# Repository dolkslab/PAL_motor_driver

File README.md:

# PAL_motor_driver

Brushed DC motor driver for RSA PAL robot. Based on arduino nano/uno + 2 DRV8871 modules to drive 24v/50W DC motors.

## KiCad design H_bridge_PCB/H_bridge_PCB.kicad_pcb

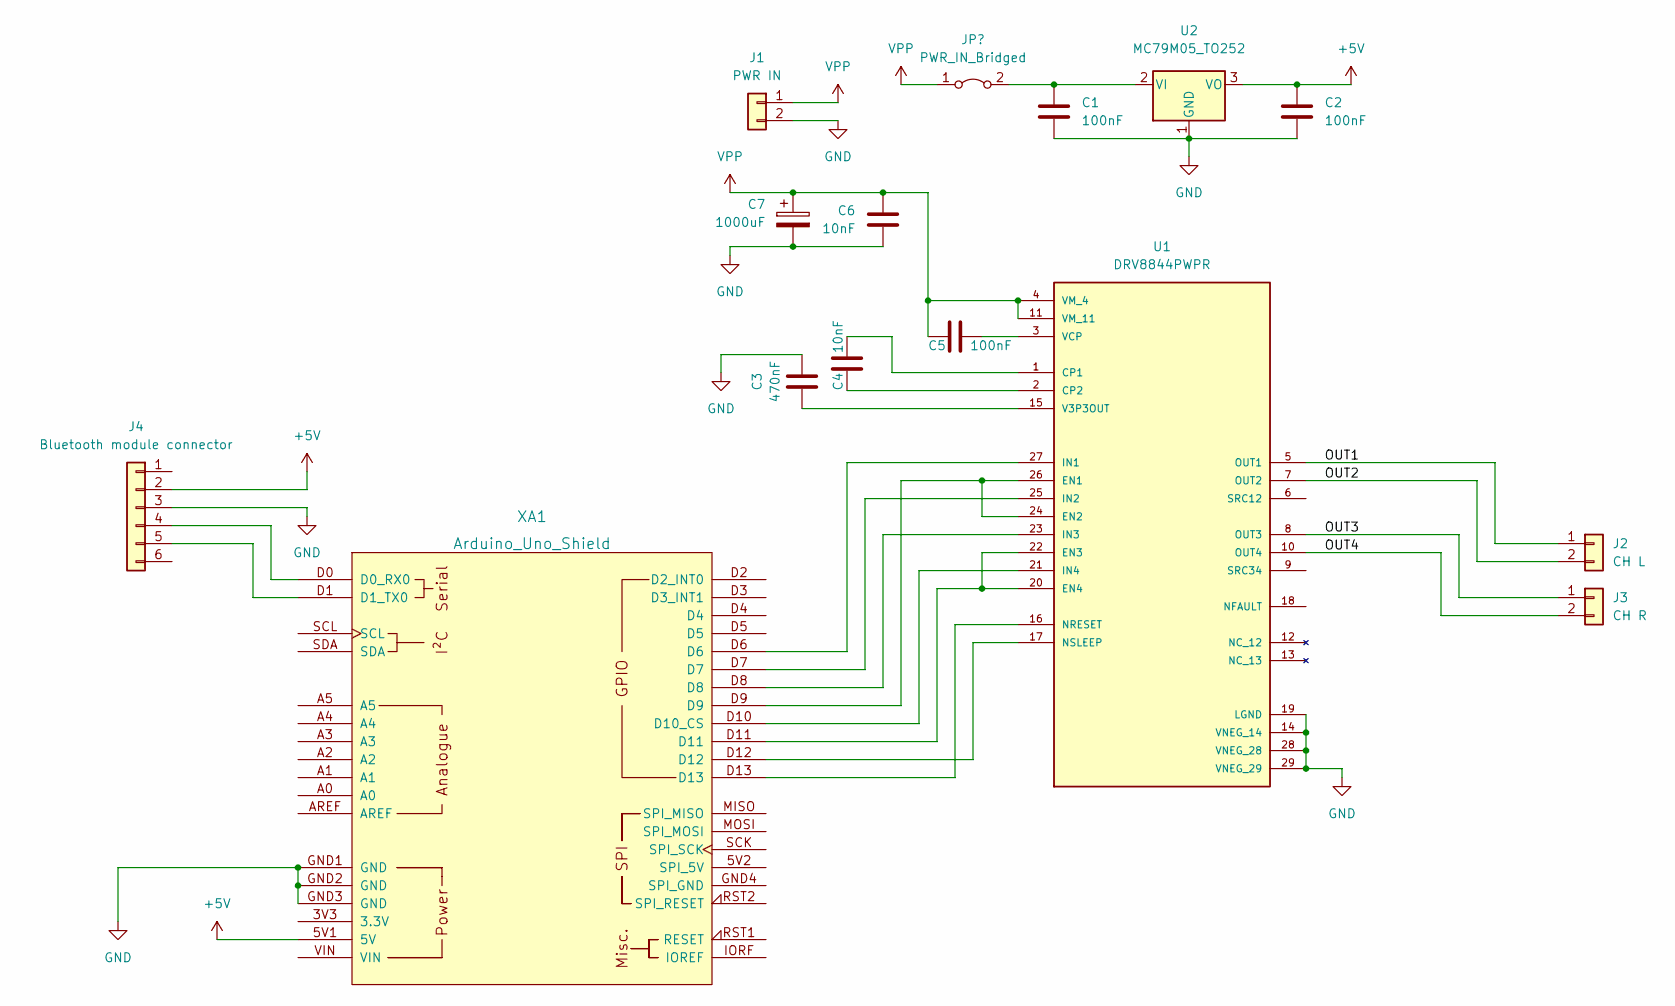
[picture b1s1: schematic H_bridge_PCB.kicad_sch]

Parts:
C1, C2, C5: 100nF; C_0603_1608Metric
C3: 470nF; C_0603_1608Metric
C4, C6: 10nF; C_0603_1608Metric
C7: 1000uF; C_Axial_L19.0mm_D8.0mm_P25.00mm_Horizontal
J1: PWR IN; TerminalBlock_MetzConnect_Type701_RT11L02HGLU_1x02_P6.35mm_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
J2: CH L; TerminalBlock_MetzConnect_Type701_RT11L02HGLU_1x02_P6.35mm_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
J3: CH R; TerminalBlock_MetzConnect_Type701_RT11L02HGLU_1x02_P6.35mm_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
J4: Bluetooth module connector; PinSocket_1x06_P2.54mm_Horizontal
U1: DRV8844PWPR; IC_DRV8844PWPR; PARTREV D
U2: MC79M05_TO252; TO-252-2
XA1: Arduino_Uno_Shield

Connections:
+5V: C2.1, J4.2, U2.3 (VO), XA1.5V1 (5V)
/OUT1: J2.1, U1.5 (OUT1)
/OUT2: J2.2, U1.7 (OUT2)
/OUT3: J3.1, U1.8 (OUT3)
/OUT4: J3.2, U1.10 (OUT4)
GND: C1.2, C2.2, C3.1, C6.2, C7.2, J1.2, J4.3, U1.14 (VNEG_14), U1.19 (LGND), U1.28 (VNEG_28), U1.29 (VNEG_29), U2.1 (GND), XA1.GND1 (GND), XA1.GND2 (GND), XA1.GND3 (GND)
unnamed 6: C1.1, U2.2 (VI); also elsewhere on the board
unnamed: C3.2, U1.15 (V3P3OUT)
unnamed: C4.1, U1.2 (CP2)
unnamed: C4.2, U1.1 (CP1)
unnamed: C5.2, U1.3 (VCP)
unnamed: U1.16 (NRESET), XA1.D13
unnamed: U1.17 (NSLEEP), XA1.D12
unnamed: U1.20 (EN4), U1.22 (EN3), XA1.D11
unnamed: U1.21 (IN4), XA1.D10 (D10_CS)
unnamed: U1.23 (IN3), XA1.D8
unnamed: U1.24 (EN2), U1.26 (EN1), XA1.D9
unnamed: U1.25 (IN2), XA1.D7
unnamed: U1.27 (IN1), XA1.D6
unnamed: J4.4, XA1.D0 (D0_RX0)
unnamed: J4.5, XA1.D1 (D1_TX0)
VPP: C5.1, C6.1, C7.1, J1.1, U1.4 (VM_4), U1.11 (VM_11); also elsewhere on the board

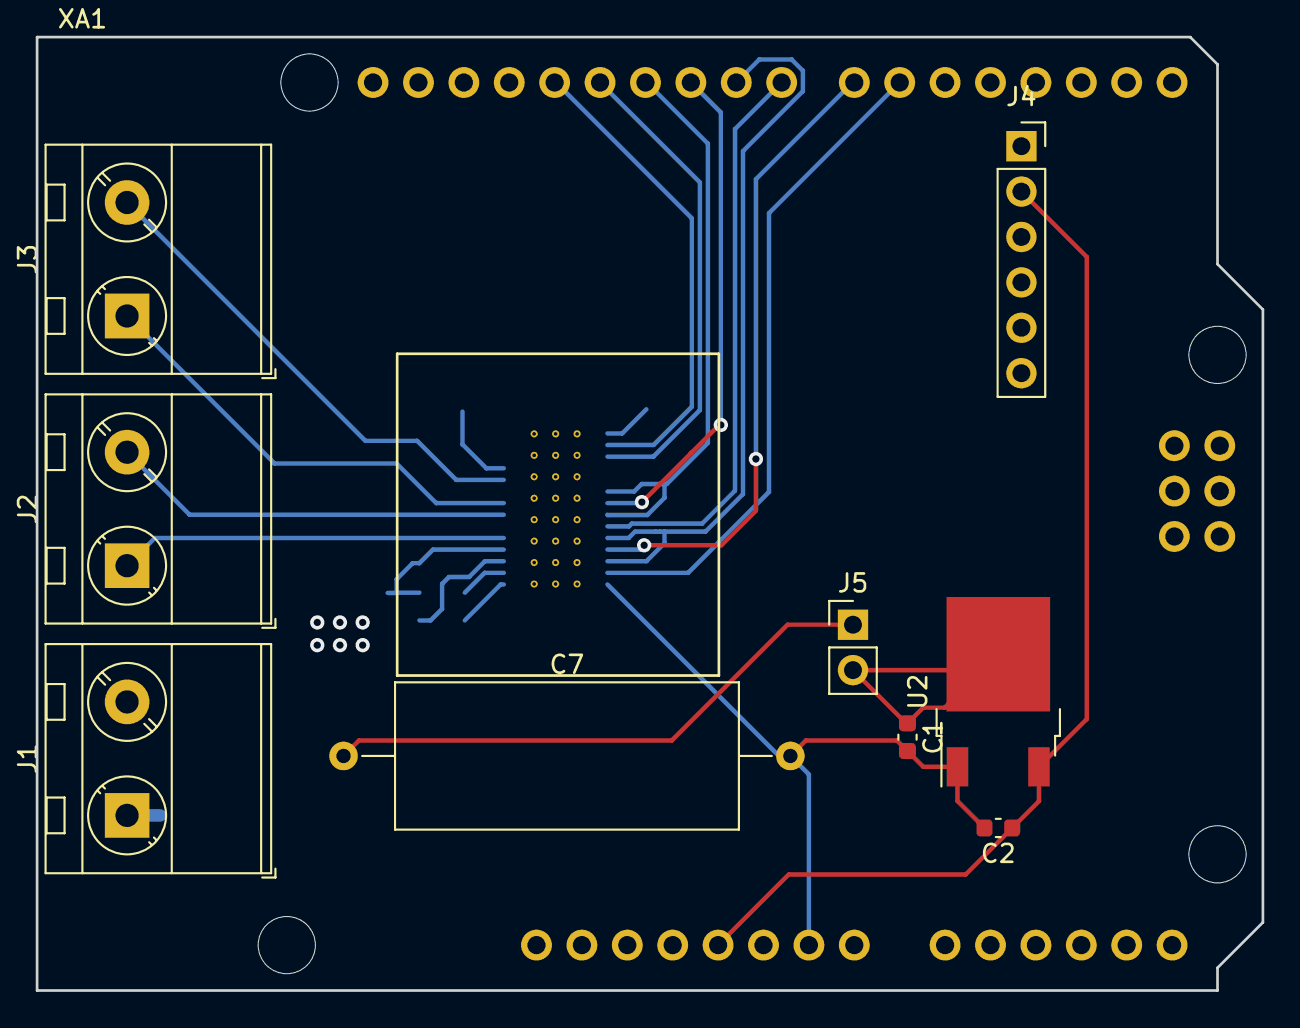
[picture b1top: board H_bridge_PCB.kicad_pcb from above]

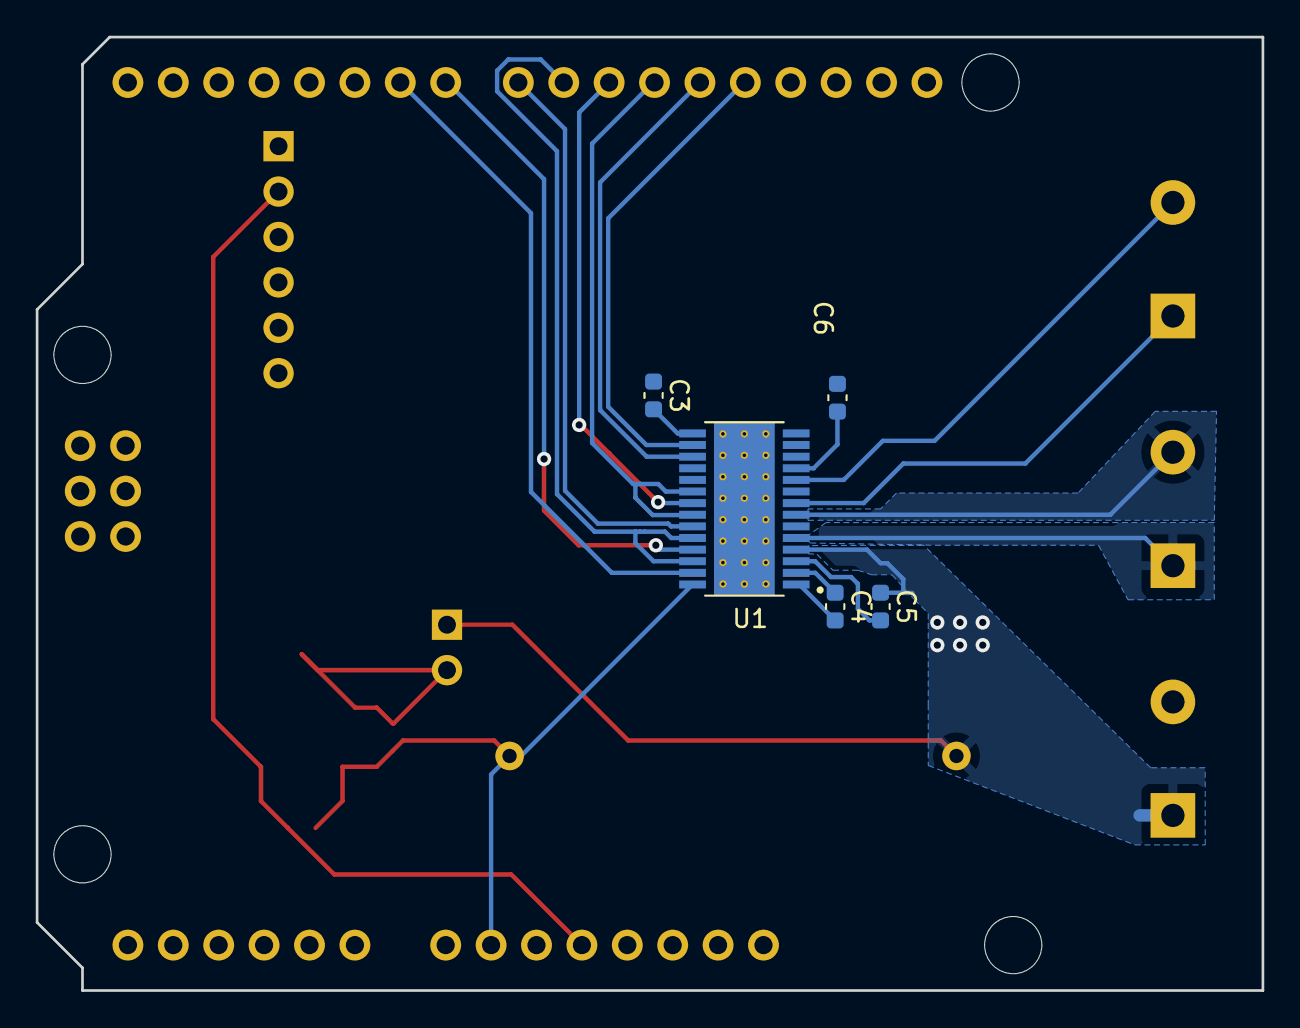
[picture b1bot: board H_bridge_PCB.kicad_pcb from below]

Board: 2 copper layers, 68.6 x 53.3 mm, 15 parts (5 on the bottom side), 22 nets.

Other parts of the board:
J5: PWR IN jumper; PinHeader_1x02_P2.54mm_Vertical

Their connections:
unnamed 6: J5.2; also elsewhere on the board
VPP: J5.1; also elsewhere on the board

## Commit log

2022-06-13 start work on PI velocity control
2022-06-13 Delete .~lock.DBL motor inventory oct 2013.xls#
    this shouldnt be here lol
2022-06-28 implement new motor driver compatibility
